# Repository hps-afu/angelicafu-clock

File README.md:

# angelicafu-clock
 My first HPS clock

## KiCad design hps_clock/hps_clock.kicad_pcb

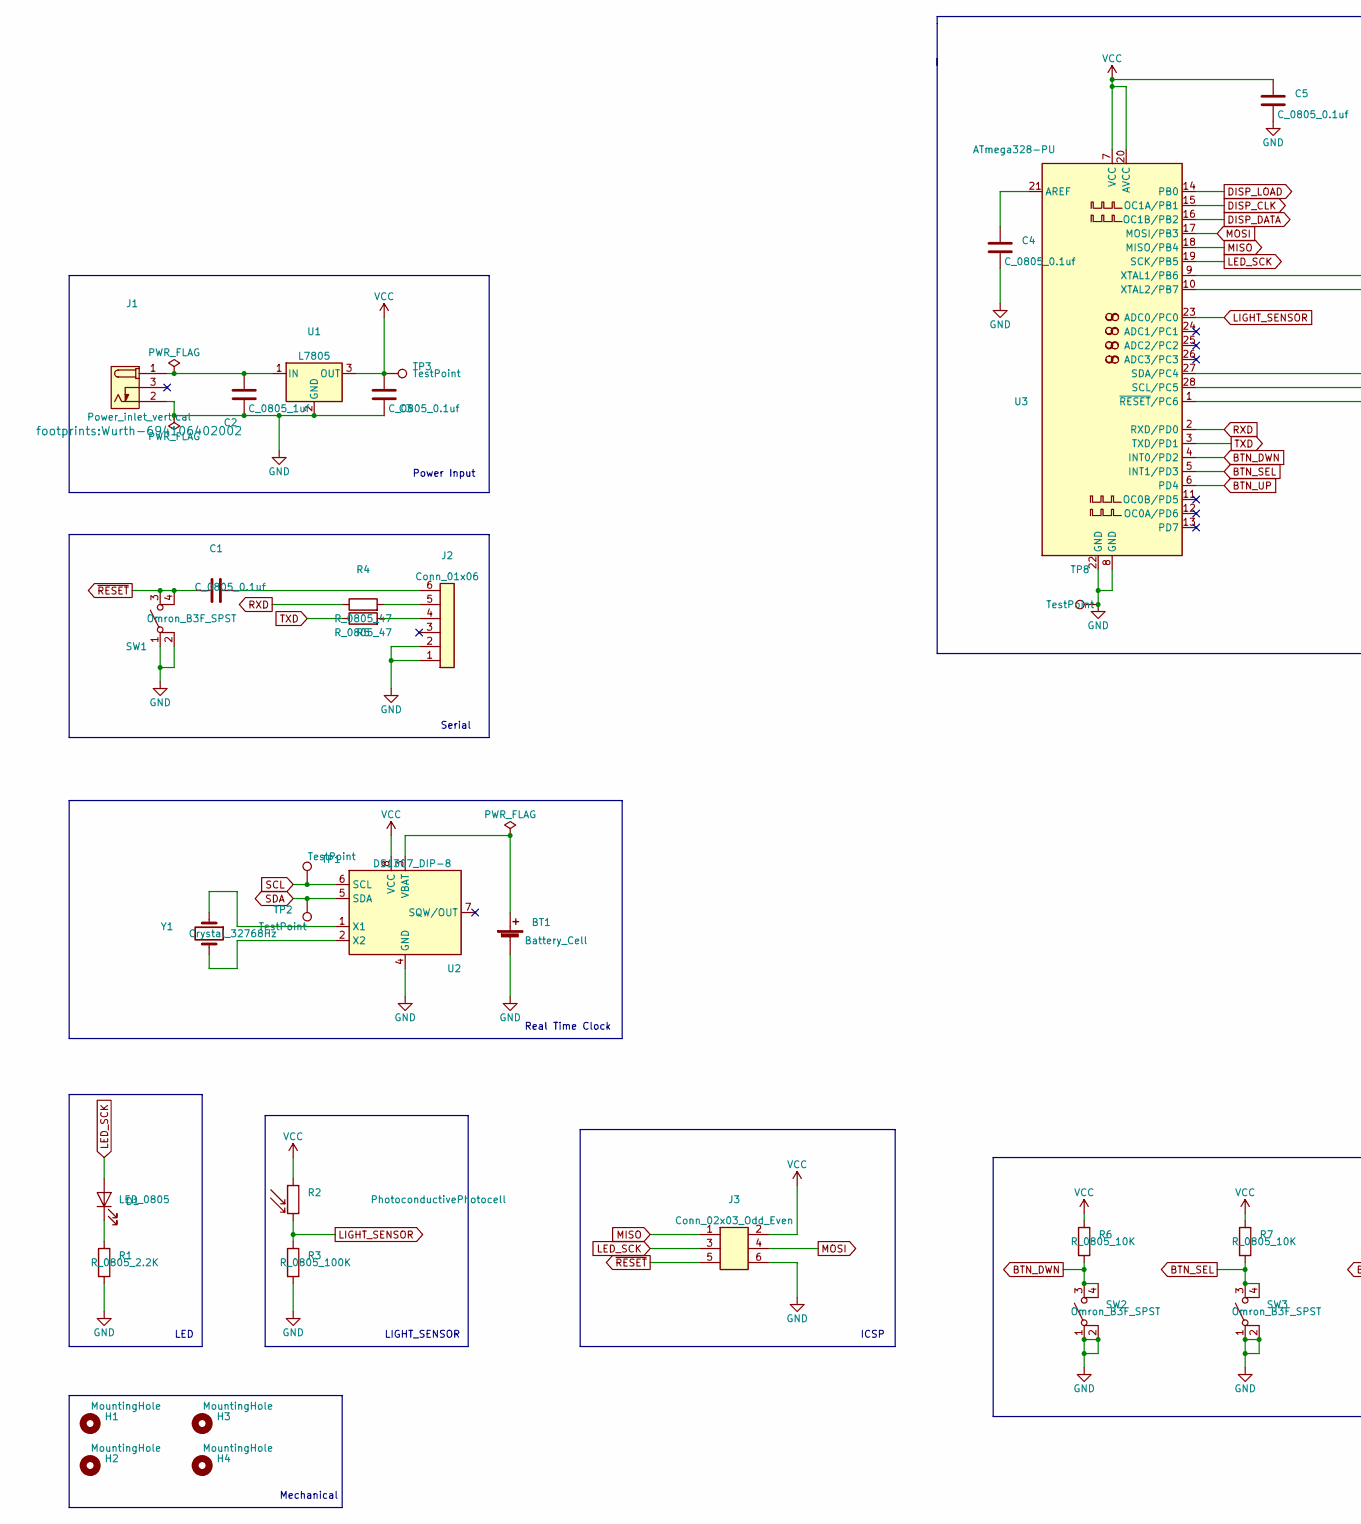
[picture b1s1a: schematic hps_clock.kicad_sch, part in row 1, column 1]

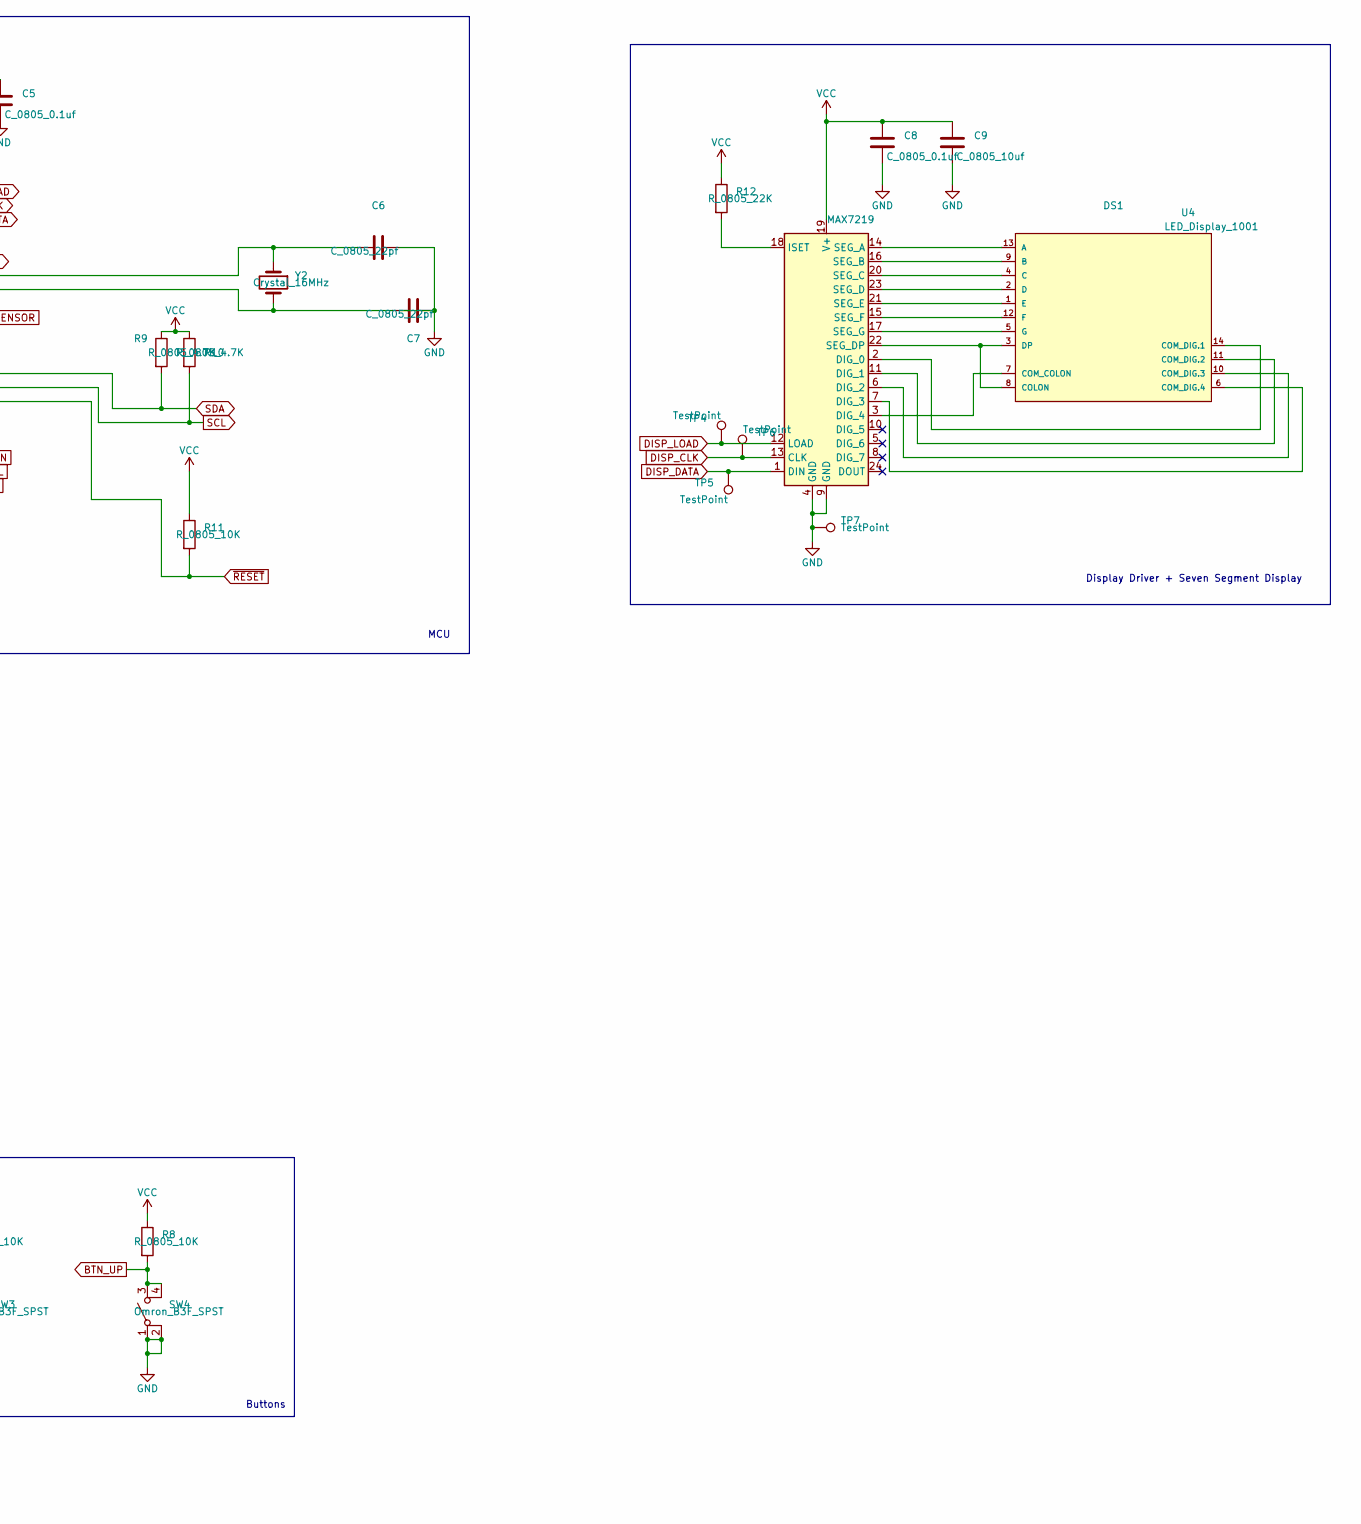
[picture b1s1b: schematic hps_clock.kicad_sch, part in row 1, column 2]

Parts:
BT1: Battery_Cell; BatteryHolder_Keystone_106_1x20mm; MPN BS-7; Digikey PN BS-7-ND
C1, C3, C4, C5, C8: C_0805_0.1uf; C_0805_2012Metric; Voltage N/A; Tolerance N/A; MPN 08055C104KAT2A; Digikey PN 478-1395-1-ND
C2: C_0805_1uf; C_0805_2012Metric; Voltage N/A; Tolerance N/A; MPN CC0805KKX7R8BB105; Digikey PN 311-1456-1-ND
C6, C7: C_0805_22pf; C_0805_2012Metric; Voltage N/A; Tolerance N/A; MPN CC0805JRNPO9BN220; Digikey PN 311-1103-1-ND
C9: C_0805_10uf; C_0805_2012Metric; Voltage N/A; Tolerance N/A; MPN GRM21BR61E106KA73L; Digikey PN 490-5523-1-ND
D1: LED_0805; LED_0805_2012Metric; MPN 150080RS75000; Digikey PN 732-4984-1-ND
DS1: LED_Display_1001; Adafruit-1001-0-0-MFG; forward voltage 3.2V; reverse voltage 5V; mouser part number 485-1001; digikey description WHITE 7-SEGMENT CLOCK DISPLAY
H1, H2, H3, H4: MountingHole; MountingHole_3.2mm_M3
J1: Power_inlet_vertical; Wurth-694106402002; MPN 694106402002; Digikey PN 732-5931-ND
J2: Conn_01x06; PinHeader_1x06_P2.54mm_Vertical; MPN 61300611121; Digikey PN 732-5319-ND
J3: Conn_02x03_Odd_Even; PinHeader_2x03_P2.54mm_Vertical; MPN PRPC003DAAN-RC; Digikey PN S2011EC-03-ND
R1: R_0805_2.2K; R_0805_2012Metric; Tolerance N/A; MPN N/A; Digikey PN 311-2.20KCRCT-ND
R2: PhotoconductivePhotocell; R_LDR_4.9x4.2mm_P2.54mm_Vertical; Voltage N/A; Tolerance N/A; MPN PDV-P8103; Digikey PN PDV-P8103-ND
R3: R_0805_100K; R_0805_2012Metric; Tolerance N/A; MPN RC0805FR-07100KL; Digikey PN 311-100KCRCT-ND
R4, R5: R_0805_47; R_0805_2012Metric; Tolerance N/A; Mouser PN N/A; Digikey PN RC0805FR-0747RL
R6, R7, R8, R11: R_0805_10K; R_0805_2012Metric; Tolerance N/A; MPN RC0805FR-0710KL; Digikey PN 311-10.0KCRCT-ND
R9, R10: R_0805_4.7K; R_0805_2012Metric; Tolerance N/A; MPN RC0805FR-074K7L; Digikey PN 311-4.70KCRCT-ND
R12: R_0805_22K; R_0805_2012Metric; Tolerance N/A; MPN RC0805FR-0722KL; Digikey PN 311-22.0KCRCT-ND
SW1, SW2, SW3, SW4: Omron_B3F_SPST; SW_SPST_Omron_B3FS-100xP; MPN B3FS-1000P; Digikey PN SW423CT-ND
TP1, TP2, TP3, TP4, TP5, TP6, TP7, TP8: TestPoint; TestPoint_THTPad_D2.0mm_Drill1.0mm
U1: L7805; TO-252-2; MPN L7805CDT-TR; Digikey PN 497-7255-1-ND
U2: DS1307_DIP-8; DIP-8_W7.62mm; MPN A 08-LC-TT; Digikey PN AE9986-ND
U3: ATmega328-PU; DIP-28_W7.62mm; MPN ED281DT; Digikey PN ED3050-5-ND
U4: MAX7219; DIP-24_W7.62mm; MPN ED241DT; Digikey PN ED3049-5-ND
Y1: Crystal_32768Hz; Crystal_SMD_2Pin_3.2x1.5mm; MPN Q 0,032768-JTX310-12,5-20-T1-HMR-50K-LF; Digikey PN 1908-1314-1-ND
Y2: Crystal_16MHz; Crystal_SMD_HC49-SD; MPN ECS-160-20-5PXDN-TR; Digikey PN XC1299CT-ND

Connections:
BTN_DWN: R6.2, SW2.3 (B), SW2.4 (B), U3.4 (INT0/PD2)
BTN_SEL: R7.2, SW3.3 (B), SW3.4 (B), U3.5 (INT1/PD3)
BTN_UP: R8.2, SW4.3 (B), SW4.4 (B), U3.6 (PD4)
DISP_CLK: TP6.1, U3.15 (OC1A/PB1), U4.13 (CLK)
DISP_DATA: TP5.1, U3.16 (OC1B/PB2), U4.1 (DIN)
DISP_LOAD: TP4.1, U3.14 (PB0), U4.12 (LOAD)
GND: BT1.2 (-), C2.2, C3.2, C4.2, C5.2, C6.1, C7.1, C8.2, C9.2, J1.2 (OUT), J2.1, J2.2, J3.6, R1.2, R3.2, SW1.1 (A), SW1.2 (A), SW2.1 (A), SW2.2 (A), SW3.1 (A), SW3.2 (A), SW4.1 (A), SW4.2 (A), TP7.1, TP8.1, U1.2 (GND), U2.4 (GND), U3.8 (GND), U3.22 (GND), U4.4 (GND), U4.9 (GND)
LED_SCK: D1.2 (A), J3.3, U3.19 (SCK/PB5)
LIGHT_SENSOR: R2.2, R3.1, U3.23 (ADC0/PC0)
MISO: J3.1, U3.18 (MISO/PB4)
MOSI: J3.4, U3.17 (MOSI/PB3)
unnamed: BT1.1 (+), U2.3 (VBAT)
unnamed: C1.2, J2.6
unnamed: C2.1, J1.1 (POLE), U1.1 (IN)
unnamed: C4.1, U3.21 (AREF)
unnamed: C6.2, U3.9 (XTAL1/PB6), Y2.1
unnamed: C7.2, U3.10 (XTAL2/PB7), Y2.2
unnamed: D1.1 (K), R1.1
unnamed: DS1.1 (E), U4.21 (SEG_E)
unnamed: DS1.2 (D), U4.23 (SEG_D)
unnamed: DS1.3 (DP), DS1.8 (COLON), U4.22 (SEG_DP)
unnamed: DS1.4 (C), U4.20 (SEG_C)
unnamed: DS1.5 (G), U4.17 (SEG_G)
unnamed: DS1.6 (COM_DIG.4), U4.7 (DIG_3)
unnamed: DS1.7 (COM_COLON), U4.3 (DIG_4)
unnamed: DS1.9 (B), U4.16 (SEG_B)
unnamed: DS1.10 (COM_DIG.3), U4.6 (DIG_2)
unnamed: DS1.11 (COM_DIG.2), U4.11 (DIG_1)
unnamed: DS1.12 (F), U4.15 (SEG_F)
unnamed: DS1.13 (A), U4.14 (SEG_A)
unnamed: DS1.14 (COM_DIG.1), U4.2 (DIG_0)
unnamed: J2.4, R5.2
unnamed: J2.5, R4.2
unnamed: R12.2, U4.18 (ISET)
unnamed: U2.1 (X1), Y1.1
unnamed: U2.2 (X2), Y1.2
RXD: R4.1, U3.2 (RXD/PD0)
SCL: R10.2, TP1.1, U2.6 (SCL), U3.28 (SCL/PC5)
SDA: R9.2, TP2.1, U2.5 (SDA), U3.27 (SDA/PC4)
TXD: R5.1, U3.3 (TXD/PD1)
VCC: C3.1, C5.1, C8.1, C9.1, J3.2, R2.1, R6.1, R7.1, R8.1, R9.1, R10.1, R11.1, R12.1, TP3.1, U1.3 (OUT), U2.8 (VCC), U3.7 (VCC), U3.20 (AVCC), U4.19 (V+)
~RESET: C1.1, J3.5, R11.2, SW1.3 (B), SW1.4 (B), U3.1 (~RESET/PC6)

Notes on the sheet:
Serial
Power Input
ICSP
LIGHT_SENSOR
LED
Mechanical
Display Driver + Seven Segment Display
Real Time Clock
Buttons
MCU

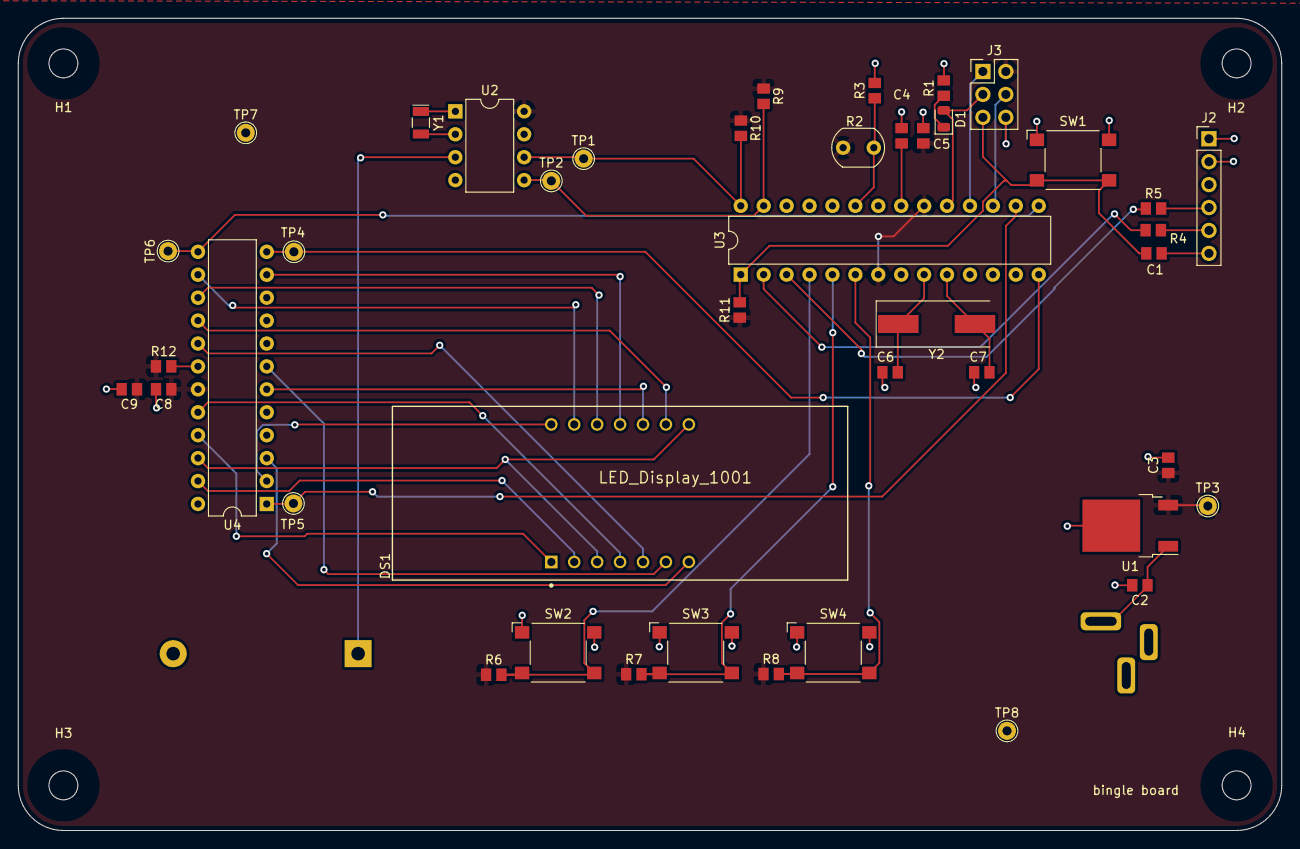
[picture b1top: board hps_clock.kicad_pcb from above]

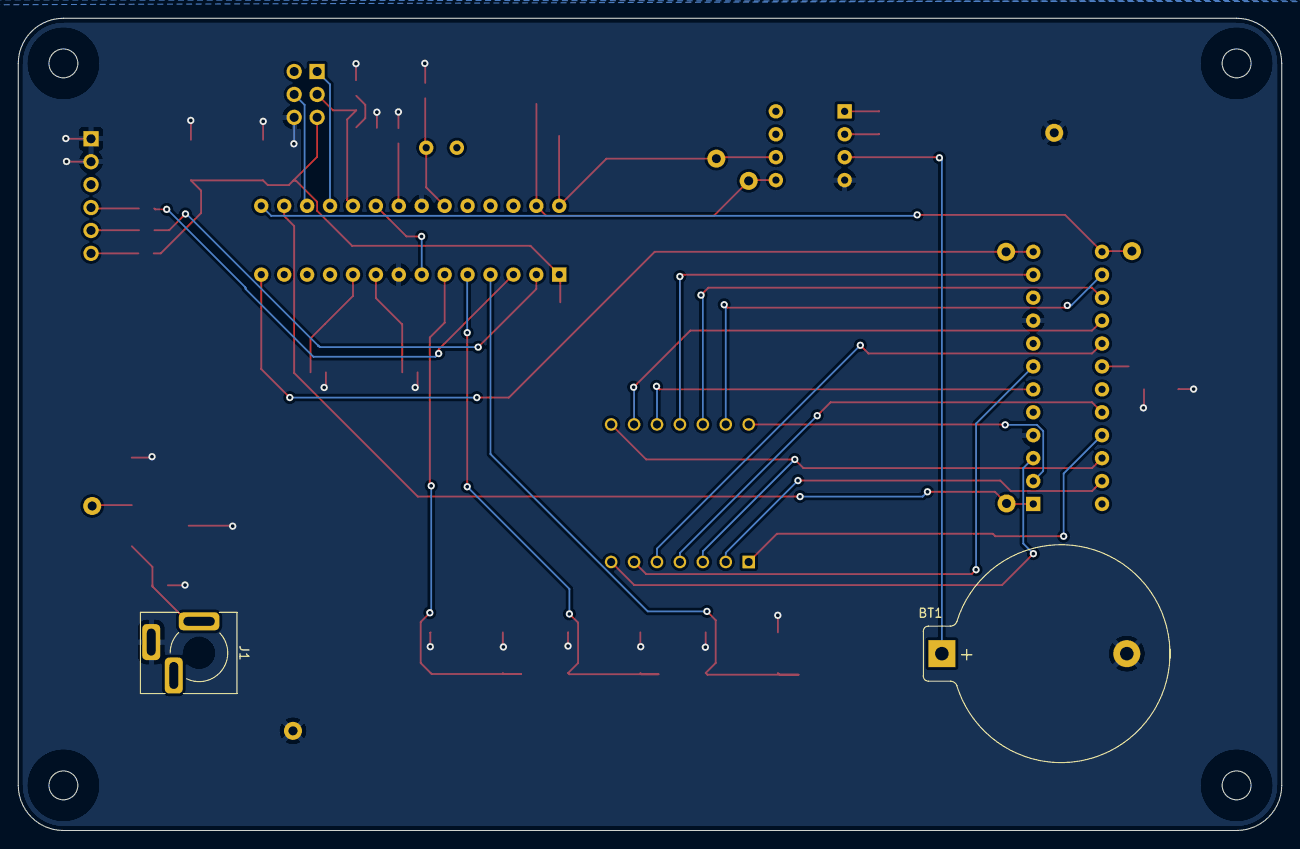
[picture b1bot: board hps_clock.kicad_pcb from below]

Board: 2 copper layers, 140.0 x 90.0 mm, 49 parts (2 on the bottom side), 42 nets.

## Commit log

2022-06-03 My first design commit
2022-06-10 clock schematic v1
2022-06-14 mcu schematic
2022-06-17 schematic w2
2022-06-17 schematic w2 v2
2022-06-17 schematic w2 v2.1
2022-06-17 schematic w2 v2.2
2022-06-17 schematic w2 v2.3
2022-06-17 schematic w2 v2.4
2022-06-28 week3
2022-06-29 week3/4
2022-07-14 schematic done..?
2022-07-18 schematic_fin
2022-07-18 schematic_final
2022-07-18 pcb_first_draft
2022-07-19 pcb_second_draft
2022-07-20 pcb_3
2022-07-21 pcb_4
2022-07-21 pcb_5
2022-07-22 pcb_6
2022-07-22 pcb_7
2022-07-22 pcb_8
2022-07-24 gerber out
2022-07-25 gerber out 2
